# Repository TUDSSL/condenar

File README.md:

# TURNER Games Console

This is the official public repository for the TURNER battery-free gaming console.

<p align="center">
  <sub><strong>Figure 1.</strong> The battery-free TURNER console in action. Turning the crank enables weapon firing in DOOM while simultaneously generating energy to charge TURNER’s energy-storage capacitor. The capacitor’s charging state is shown by a small indicator at the top-right of the LCD panel. TURNER integrates solar energy harvesting, follows the form factor of a modern handheld game console, and features the standard “ABXY” button configuration. The current implementation weighs 509 g; the casing measures 24 cm × 14 cm × 3 cm, and the crank measures 2 cm × 6.5 cm × 2 cm.</sub>
</p>

## System Design Rationale

Battery-free computer gaming offers a vision of sustainable interaction in which games run on hardware that does not require a battery, yet this approach introduces uncertainty due to frequent power failures. Rather than viewing these failures as limitations, this work examines how integrating energy harvesting with application design can encourage users to reimagine and work with such failures, thus shaping behaviour and supporting device use. We present TURNER, a state-of-the-art modular battery-free games console powered by a hand crank and solar cells, created as a research probe to study how energy harvesting mediates the relationship between power and interaction. 

In a subsequent mixed-methods study (N = 60), we explored the influence of energy harvesting on gameplay. Findings show significant variations in harvesting strategies, with interviews surfacing strategies for creating applications that respond to and build on the patterns of system power failure, the ergonomics of energy harvesting, and the value of embedding energy generation into play. Our work offers insights for interactive, sustainable battery-free computers.

## Repository Structure

- [/Hardware](https://github.com/tudssl/condenar/tree/master/Hardware): This folder contains the source files for the hardware used in this project.
- [/Software](https://github.com/tudssl/condenar/tree/master/Software): The folder contains the software used in the TURNER console (including console firmware, apps, and logging software).
- [/Data](https://github.com/tudssl/condenar/tree/master/Data): This folder contains the data and data analysis scripts used in the TURNER user study.
- [/Doc-images](https://github.com/TUDSSL/condenar/tree/master/Doc-images): This folder contains images of the TURNER console. 

## TURNER System Description

<p align="center">
  <sub><strong>Figure 2.</strong> TURNER system implementation: (A) back of the COM50H5M81XLC transflective LCD screen; (B) logging module using an Espressif Systems ESP32 PICO Series microcontroller; (C) Central Processing Unit (CPU) module using an Ambiq Apollo4 MCU; (D) power management; (E) logging module battery; (F) solar module implemented around the Analog Devices LTC3129 Maximum Power Point Tracking (MPPT) buck-boost energy harvester; (G) crank module; (H) 6V 1.5F Kyocera AVX-SCM supercapacitor (SCMR22H155PSBB0); (I) ambient light sensor; (J) energy module connection points; (K) “ABXY” buttons; (L) solar panel connection on the front of the system casing. Eight ExCellLight EXL10-4V170 high-performance solar cells (50 mm × 20 mm each) are deployed; (M) joystick; (N) Universal Serial Bus (USB) port; (O) left trigger button; (P) right trigger button. The battery is used <em>only</em> to power the logging module and during the battery-powered console configuration experimental condition.</sub>
</p>

## TURNER User Study

The user study of TURNER employed a mixed-methods approach, combining console log data, questionnaire responses, and post-study interviews. The study was [pre-registed at Open Science Framework (OSF)](http://osf.io/7fp2w). 

### Quantitative Analysis

A range of statistical tests were used to assess the significance of effects in our log and questionnaire data. Parametric tests were applied when assumptions of normality, from Shapiro-Wilk, and homoscedasticity, from Levene's tests, were met. To analyse differences among more than two groups, we used Analysis of Variance (ANOVA) for between-subjects designs and repeated-measures ANOVA for within-subjects designs when parametric assumptions held, and Kruskal–Wallis or Friedman tests when non-parametric, respectively. Significant results were followed by post-hoc pairwise comparisons using Tukey’s HSD (parametric) or Dunn’s test with Bonferroni correction (non-parametric). For comparisons between two groups, we used independent samples t-tests or Mann-Whitney U tests, as appropriate. 

### Qualitative Analysis

We analysed post-study interviews using inductive thematic analysis, following the six-phase guidance proposed by [Braun and Clarke](https://www.tandfonline.com/doi/abs/10.1191/1478088706qp063oa). Coding was inductive, with initial descriptive and in vivo codes generated through repeated engagement with participants’ responses. Codes were iteratively refined and grouped into broader patterns through multiple rounds of analysis. 

## How to Cite This Work

The results of this project will be published in a peer-reviewed academic publication (from which all technical figures and most of the text in this file originate). Details of the publication are as follows.

* **Authors and the project team:** [James Scott Broadhead](https://scholar.google.com/citations?user=sMDFHlMAAAAJ), [Jasper de Winkel](https://jasperdewinkel.com), [Alejandro Cabrerizo Martinez de La Puente](https://www.linkedin.com/in/alejandro-cabrerizo-03780b136), [Himanshu Verma](https://vermahimanshu.com), [Przemysław Pawełczak](http://www.pawelczak.net)
* **Publication title:** _Connecting Power and Play: Investigating Interactive Energy Harvesting in Battery-Free Gaming_

<!--
* **Pulication venue:** [Proceedings of the 2026 CHI Conference on Human Factors in Computing Systems (CHI '26), April 13-17, 2026, Barcelona, Spain](https://dl.acm.org/)
* **Link to publication:** https://doi.org/10.1145/3772318.3790831 (Open Access)
* **Link to ACM CHI 2026 conference presentation video:** https://www.youtube.com/watch?
-->

<!--
To cite this publication please use the following BiBTeX entry.

```
@article{broadhead:chi:2026:turner,
  title = {Connecting Power and Play: Investigating Interactive Energy Harvesting in Battery-Free Gaming},
  author = {James Scott {Broadhead} and Jasper {de Winkel} and Alejandro Cabrerizo Martinez {de La Puente} and Himanshu {Verma} and Przemys{\l}aw {Pawe{\l}czak}},
  journal = {Proc. ACM Conference on Human Factors in Computing Systems (ACM CHI)},
  month =  apr # " 13--17",
  year = {2026},
  pages = {--},
  address = {Barcelona, Spain},
  publisher = {ACM}
}
```
-->

## Copyright

Copyright (C) 2026 TU Delft Embedded Systems Group/Sustainable Systems Laboratory.

MIT License or otherwise specified. See [license](https://github.com/TUDSSL/CONDENAR/blob/master/LICENSE) file for details.

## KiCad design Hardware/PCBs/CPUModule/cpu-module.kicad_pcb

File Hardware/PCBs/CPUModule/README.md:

# CPU-Module

KiCad project of the CPU module, including the schematic, PCB layout and BOM.

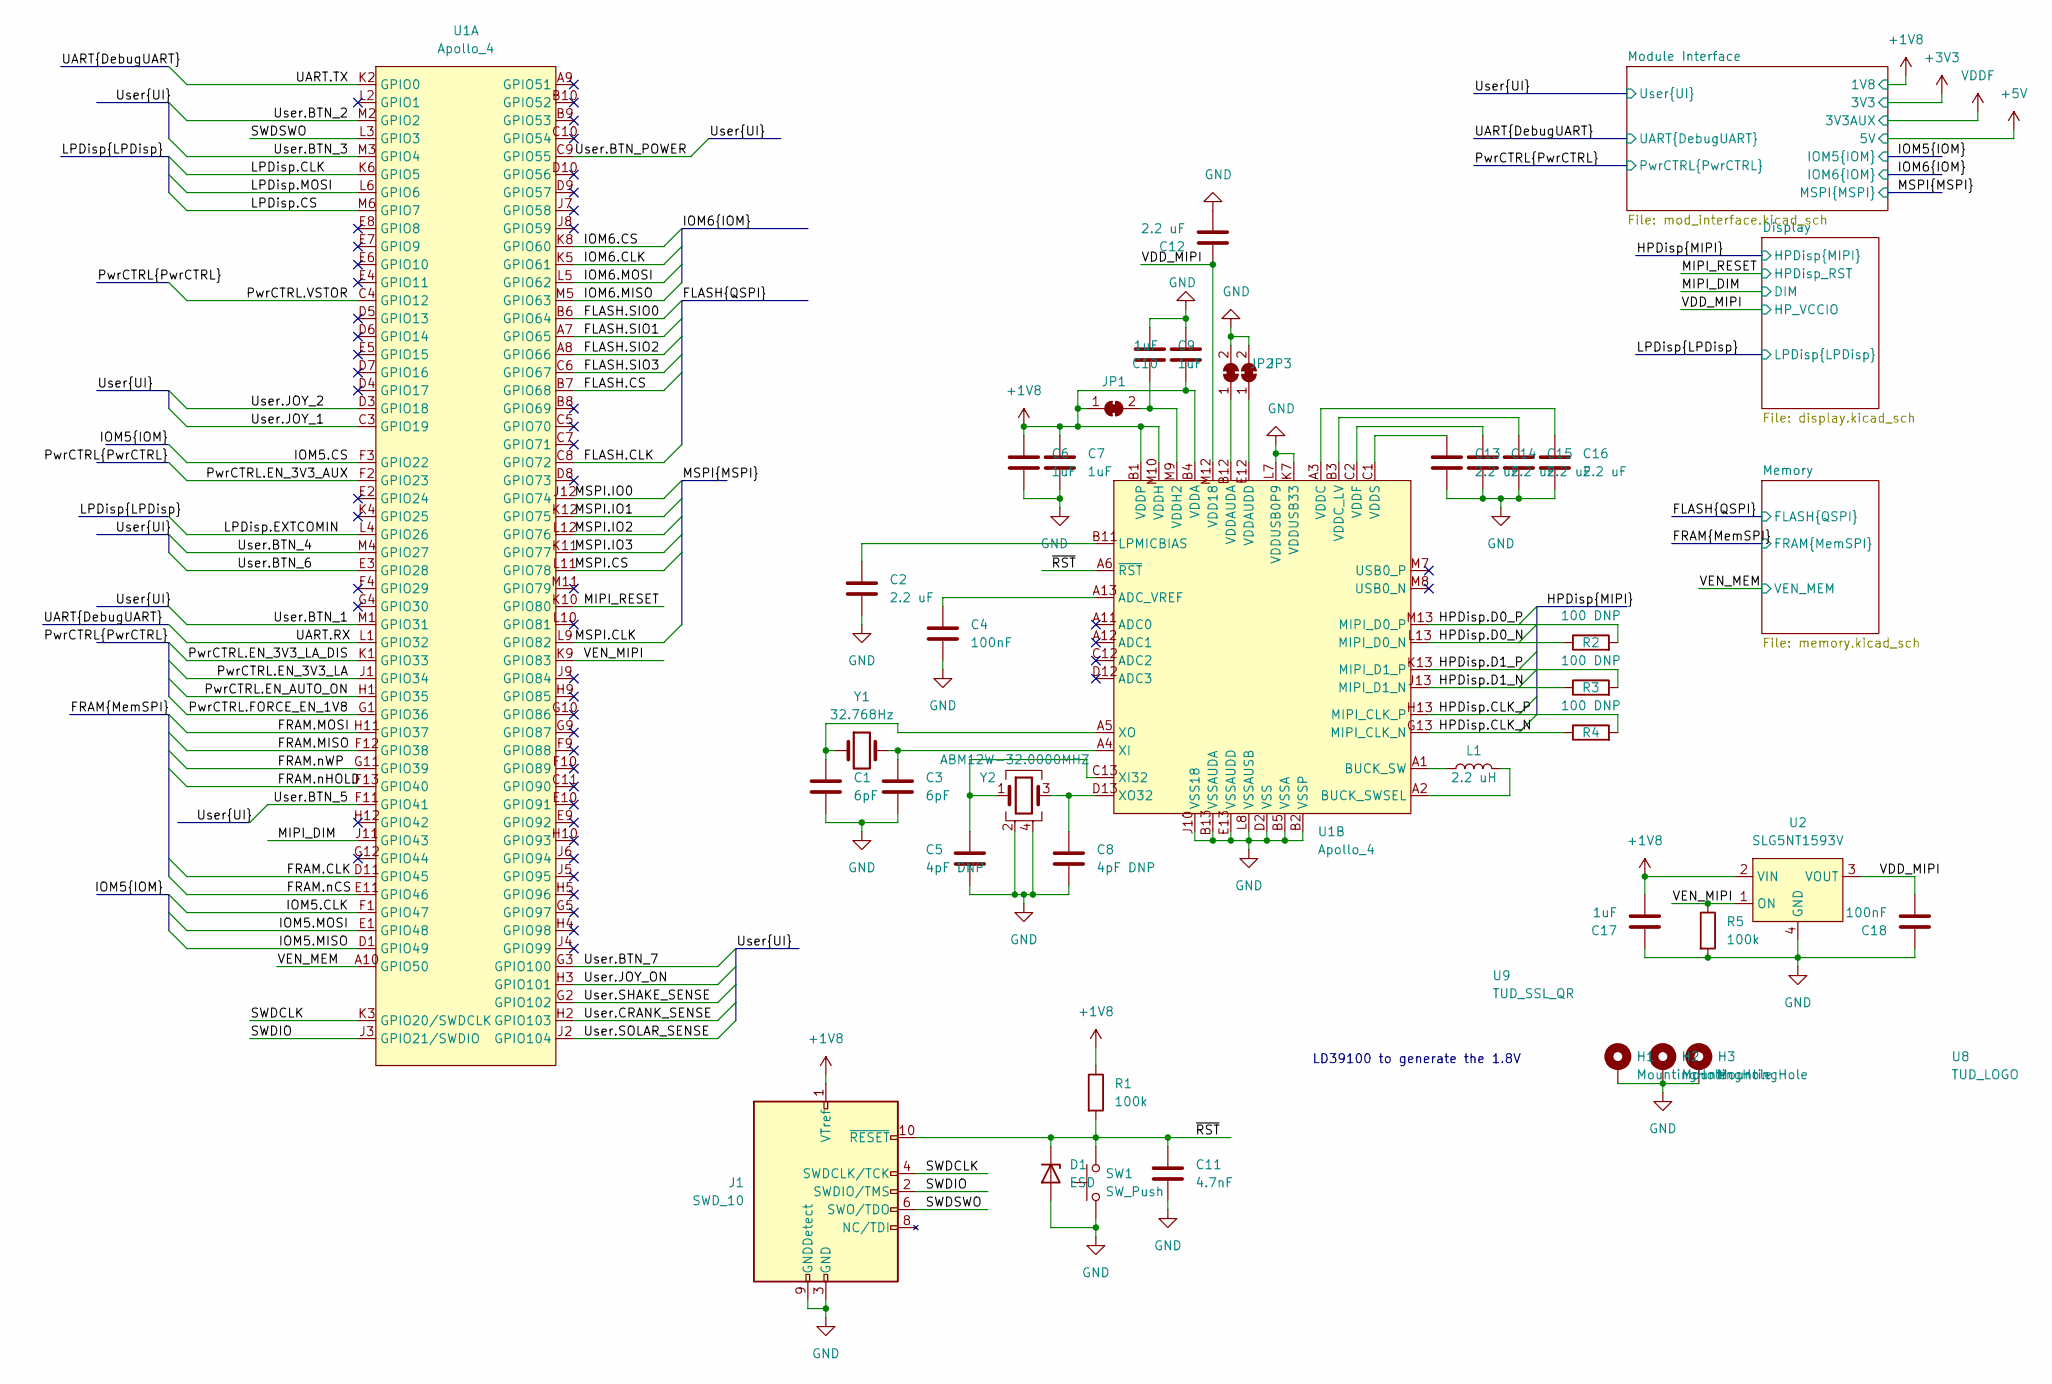
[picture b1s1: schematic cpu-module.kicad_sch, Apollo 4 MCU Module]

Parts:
C1, C3: 6pF; C_0402_1005Metric; MPN CC0402BRNPO9BN6R0
C2, C12, C13, C14, C15, C16: 2.2 uF; C_0201_0603Metric; MPN GRM033R61A225KE47D
C4, C18: 100nF; C_0402_1005Metric; MPN GRM155R71C104KA88J
C5, C8: 4pF DNP; C_0402_1005Metric; MPN CQ0402ARNPO9BN4R0
C6, C7, C9, C10: 1uF; C_0201_0603Metric; MPN GRM033C81A105ME05D
C11: 4.7nF; C_0201_0603Metric; MPN GRM033R61E472KA12D
C17: 1uF; C_0402_1005Metric; MPN CL05A105KP5NNNC
D1: ESD; D_SOD-523; MPN PESD5V0X1UB
H1, H2, H3: MountingHole; MountingHole_2.2mm_M2_Pad_Via
J1: SWD_10; ftsh-105-01-f-dv-k; MPN ftsh-105-01-f-dv-k
JP1, JP2, JP3: SolderJumper_2_Bridged; SolderJumper-small-nc
L1: 2.2 uH; L_0805_2012Metric; MPN DFE201210U-2R2M=P2
R1, R5: 100k; R_0402_1005Metric; MPN ERJ-2RKF1003X
R2, R3, R4: 100 DNP; R_0201_0603Metric; MPN CRCW0201100RFNED
SW1: SW_Push; SW_SPST_B3U-1000P; MPN B3U-1000P
U1: Apollo_4; Apollo4-BGA-156_13x12_5.0x5.0mm; MPN Apollo 4
U2: SLG5NT1593V; MPN SLG5NT1593V
U8: TUD_LOGO; DELFT_LOGO2
U9: TUD_SSL_QR; TUDSSL
Y1: 32.768Hz; Crystal_SMD_MicroCrystal_CM9V-T1A-2Pin_1.6x1.0mm; MPN 9HT12-32.768KDZY
Y2: ABM12W-32.0000MHZ; Crystal_SMD_Abracon_ABM12B-4Pin_1.6x1.2mm; MPN ABM12W-32.0000MHZ-6-D1X-T3

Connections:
+1V8: C6.1, C7.1, C10.1, C17.2, J1.1 (VTref), JP1.1 (A), R1.1, U1.B1 (VDDP), U1.B4 (VDDA), U1.M10 (VDDH), U2.2 (VIN); also elsewhere on the board
/FLASH.CLK: U1.C8 (GPIO72); also elsewhere on the board
/FLASH.CS: U1.B7 (GPIO68); also elsewhere on the board
/FLASH.SIO0: U1.B6 (GPIO64); also elsewhere on the board
/FLASH.SIO1: U1.A7 (GPIO65); also elsewhere on the board
/FLASH.SIO2: U1.A8 (GPIO66); also elsewhere on the board
/FLASH.SIO3: U1.C6 (GPIO67); also elsewhere on the board
/FRAM.CLK: U1.D11 (GPIO45); also elsewhere on the board
/FRAM.MISO: U1.F12 (GPIO38); also elsewhere on the board
/FRAM.MOSI: U1.H11 (GPIO37); also elsewhere on the board
/FRAM.nCS: U1.E11 (GPIO46); also elsewhere on the board
/FRAM.nHOLD: U1.F13 (GPIO40); also elsewhere on the board
/FRAM.nWP: U1.G11 (GPIO39); also elsewhere on the board
/HPDisp.CLK_N: R4.1, U1.G13 (MIPI_CLK_N); also elsewhere on the board
/HPDisp.CLK_P: R4.2, U1.H13 (MIPI_CLK_P); also elsewhere on the board
/HPDisp.D0_N: R2.1, U1.L13 (MIPI_D0_N); also elsewhere on the board
/HPDisp.D0_P: R2.2, U1.M13 (MIPI_D0_P); also elsewhere on the board
/HPDisp.D1_N: R3.1, U1.J13 (MIPI_D1_N); also elsewhere on the board
/HPDisp.D1_P: R3.2, U1.K13 (MIPI_D1_P); also elsewhere on the board
/IOM5.CLK: U1.F1 (GPIO47); also elsewhere on the board
/IOM5.CS: U1.F3 (GPIO22); also elsewhere on the board
/IOM5.MISO: U1.D1 (GPIO49); also elsewhere on the board
/IOM5.MOSI: U1.E1 (GPIO48); also elsewhere on the board
/IOM6.CLK: U1.K5 (GPIO61); also elsewhere on the board
/IOM6.CS: U1.K8 (GPIO60); also elsewhere on the board
/IOM6.MISO: U1.M5 (GPIO63); also elsewhere on the board
/IOM6.MOSI: U1.L5 (GPIO62); also elsewhere on the board
/LPDisp.CLK: U1.K6 (GPIO5); also elsewhere on the board
/LPDisp.CS: U1.M6 (GPIO7); also elsewhere on the board
/LPDisp.EXTCOMIN: U1.L4 (GPIO26); also elsewhere on the board
/LPDisp.MOSI: U1.L6 (GPIO6); also elsewhere on the board
/MIPI_DIM: U1.J11 (GPIO43); also elsewhere on the board
/MIPI_RESET: U1.K10 (GPIO80); also elsewhere on the board
/MSPI.CLK: U1.L9 (GPIO82); also elsewhere on the board
/MSPI.CS: U1.L11 (GPIO78); also elsewhere on the board
/MSPI.IO0: U1.J12 (GPIO74); also elsewhere on the board
/MSPI.IO1: U1.K12 (GPIO75); also elsewhere on the board
/MSPI.IO2: U1.L12 (GPIO76); also elsewhere on the board
/MSPI.IO3: U1.K11 (GPIO77); also elsewhere on the board
/PwrCTRL.EN_3V3_AUX: U1.F2 (GPIO23); also elsewhere on the board
/PwrCTRL.EN_3V3_LA: U1.J1 (GPIO34); also elsewhere on the board
/PwrCTRL.EN_3V3_LA_DIS: U1.K1 (GPIO33); also elsewhere on the board
/PwrCTRL.EN_AUTO_ON: U1.H1 (GPIO35); also elsewhere on the board
/PwrCTRL.FORCE_EN_1V8: U1.G1 (GPIO36); also elsewhere on the board
/PwrCTRL.VSTOR: U1.C4 (GPIO12); also elsewhere on the board
/SWDCLK: J1.4 (SWDCLK/TCK), U1.K3 (GPIO20/SWDCLK)
/SWDIO: J1.2 (SWDIO/TMS), U1.J3 (GPIO21/SWDIO)
/SWDSWO: J1.6 (SWO/TDO), U1.L3 (GPIO3)
/UART.RX: U1.L1 (GPIO32); also elsewhere on the board
/UART.TX: U1.K2 (GPIO0); also elsewhere on the board
/User.BTN_1: U1.M1 (GPIO31); also elsewhere on the board
/User.BTN_2: U1.M2 (GPIO2); also elsewhere on the board
/User.BTN_3: U1.M3 (GPIO4); also elsewhere on the board
/User.BTN_4: U1.M4 (GPIO27); also elsewhere on the board
/User.BTN_5: U1.F11 (GPIO41); also elsewhere on the board
/User.BTN_6: U1.E3 (GPIO28); also elsewhere on the board
/User.BTN_7: U1.G3 (GPIO100); also elsewhere on the board
/User.BTN_POWER: U1.C9 (GPIO55); also elsewhere on the board
/User.CRANK_SENSE: U1.H2 (GPIO103); also elsewhere on the board
/User.JOY_1: U1.C3 (GPIO19); also elsewhere on the board
/User.JOY_2: U1.D3 (GPIO18); also elsewhere on the board
/User.JOY_ON: U1.H3 (GPIO101); also elsewhere on the board
/User.SHAKE_SENSE: U1.G2 (GPIO102); also elsewhere on the board
/User.SOLAR_SENSE: U1.J2 (GPIO104); also elsewhere on the board
/VDD_MIPI: C12.1, C18.2, U1.M12 (VDD18), U2.3 (VOUT); also elsewhere on the board
/VEN_MEM: U1.A10 (GPIO50); also elsewhere on the board
/VEN_MIPI: R5.1, U1.K9 (GPIO83), U2.1 (ON)
/~RST: C11.1, D1.1 (K), J1.10 (~RESET), R1.2, SW1.2, U1.A6 (~RST)
GND: C1.2, C2.2, C3.2, C4.2, C5.2, C6.2, C7.2, C8.2, C9.2, C10.2, C11.2, C12.2, C13.2, C14.2, C15.2, C16.2, C17.1, C18.1, D1.2 (A), H1.1, H2.1, H3.1, J1.3 (GND), J1.5 (GND), J1.9 (GNDDetect), JP2.2 (B), JP3.2 (B), R5.2, SW1.1, U1.B2 (VSSP), U1.B5 (VSSA), U1.B13 (VSSAUDA), U1.D2 (VSS), U1.E13 (VSSAUDD), U1.J10 (VSS18), U1.K7 (VDDUSB33), U1.L7 (VDDUSB0P9), U1.L8 (VSSAUSB), U2.4 (GND), Y2.2, Y2.4; also elsewhere on the board
unnamed: C1.1, U1.A5 (XO), Y1.1
unnamed: C2.1, U1.B11 (LPMICBIAS)
unnamed: C3.1, U1.A4 (XI), Y1.2
unnamed: C4.1, U1.A13 (ADC_VREF)
unnamed: C5.1, U1.C13 (XI32), Y2.1
unnamed: C8.1, U1.D13 (XO32), Y2.3
unnamed: C9.1, JP1.2 (B), U1.M9 (VDDH2)
unnamed: C13.1, U1.C1 (VDDS)
unnamed: C14.1, U1.C2 (VDDF)
unnamed: C15.1, U1.B3 (VDDC_LV)
unnamed: C16.1, U1.A3 (VDDC)
unnamed: JP2.1 (A), U1.B12 (VDDAUDA)
unnamed: JP3.1 (A), U1.E12 (VDDAUDD)
unnamed: L1.1, U1.A1 (BUCK_SW)
unnamed: L1.2, U1.A2 (BUCK_SWSEL)

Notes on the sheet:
LD39100 to generate the 1.8V

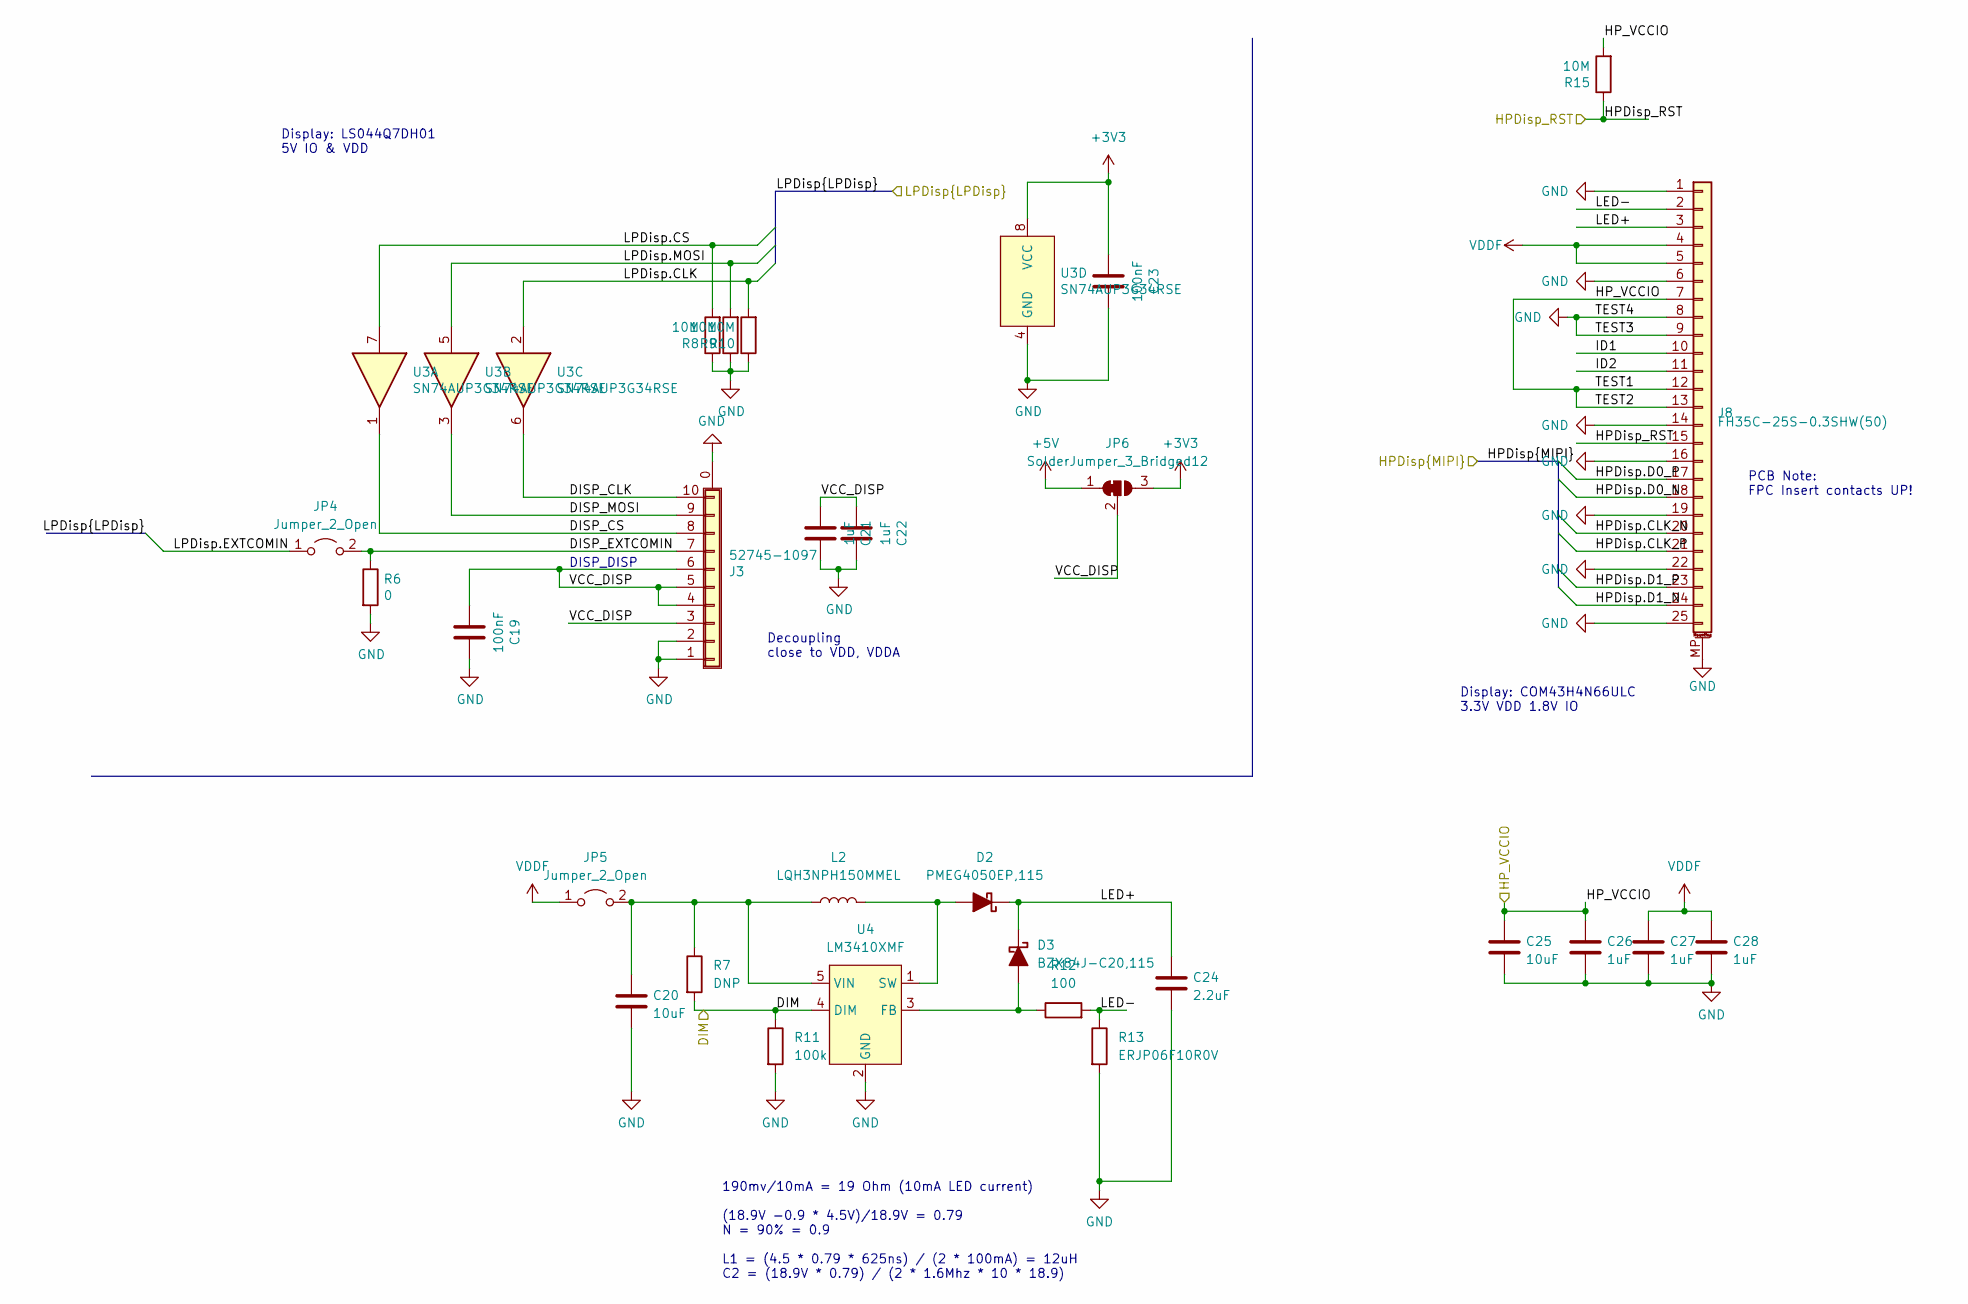
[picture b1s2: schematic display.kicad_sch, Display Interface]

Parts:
C19, C23: 100nF; C_0402_1005Metric; MPN GRM155R71C104KA88J
C20: 10uF; C_0603_1608Metric; MPN GRT188R61C106KE13D
C21, C22, C26, C27, C28: 1uF; C_0402_1005Metric; MPN CL05A105KP5NNNC
C24: 2.2uF; C_0603_1608Metric; MPN GRM188R61H225KE11D
C25: 10uF; C_0402_1005Metric; MPN CL05A106MP8NUB8
D2: PMEG4050EP,115; D_SOD-128; MPN PMEG4050EP,115
D3: BZX84J-C20,115; D_SOD-323F; MPN BZX84J-C20,115
J3: 52745-1097; FPC_10_TOP; MPN 52745-1097
J8: FH35C-25S-0.3SHW(50); FH35C-25S-0.3SHW_2Rows-27Pins-1MP_P0.60mm_Horizontal; MPN FH35C-25S-0.3SHW(50)
JP4, JP5: Jumper_2_Open; SolderJumper-small-no-150um
JP6: SolderJumper_3_Bridged12; SolderJumper-3_P1.3mm_Bridged12_RoundedPad1.0x1.5mm
L2: LQH3NPH150MMEL; VLS6045EX; MPN LQH3NPH150MMEL
R6: 0; R_0402_1005Metric; MPN ERJ-2GE0R00X
R7: DNP; R_0603_1608Metric
R8, R9, R10, R15: 10M; R_0402_1005Metric; MPN RC0402FR-0710ML
R11: 100k; R_0603_1608Metric; MPN ERJ-3EKF1003V
R12: 100; R_0603_1608Metric; MPN CRCW0603100RFKEAHP
R13: ERJP06F10R0V; R_0805_2012Metric; MPN ERJP06F10R0V
U3: SN74AUP3G34RSE; Texas_RSE_8_UQFN; MPN SN74AUP3G34RSE
U4: LM3410XMF; SOT-23-5; MPN LM3410XMF

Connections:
+3V3: C23.1, JP6.3 (B), U3.8 (VCC); also elsewhere on the board
+5V: JP6.1 (A); also elsewhere on the board
/Display/DISP_CLK: J3.10, U3.6
/Display/DISP_CS: J3.8, U3.1
/Display/DISP_EXTCOMIN: J3.7, JP4.2 (B), R6.1
/Display/DISP_MOSI: J3.9, U3.3
/Display/ID1: J8.10
/Display/ID2: J8.11
/Display/LED+: C24.1, D2.1 (K), D3.1 (K), J8.3
/Display/LED-: J8.2, R12.2, R13.1
/Display/VCC_DISP: C19.1, C21.1, C22.1, J3.3, J3.4, J3.5, J3.6, JP6.2 (C)
/HPDisp.CLK_N: J8.20; also elsewhere on the board
/HPDisp.CLK_P: J8.21; also elsewhere on the board
/HPDisp.D0_N: J8.18; also elsewhere on the board
/HPDisp.D0_P: J8.17; also elsewhere on the board
/HPDisp.D1_N: J8.24; also elsewhere on the board
/HPDisp.D1_P: J8.23; also elsewhere on the board
/LPDisp.CLK: R10.2, U3.2; also elsewhere on the board
/LPDisp.CS: R8.2, U3.7; also elsewhere on the board
/LPDisp.EXTCOMIN: JP4.1 (A); also elsewhere on the board
/LPDisp.MOSI: R9.2, U3.5; also elsewhere on the board
/MIPI_DIM: R7.2, R11.1, U4.4 (DIM); also elsewhere on the board
/MIPI_RESET: J8.15, R15.1; also elsewhere on the board
/VDD_MIPI: C25.1, C26.1, J8.7, J8.12, J8.13, R15.2; also elsewhere on the board
GND: C19.2, C20.2, C21.2, C22.2, C23.2, C24.2, C25.2, C26.2, C27.2, C28.2, J3.0 (Shield), J3.1, J3.2, J8.1, J8.6, J8.8, J8.9, J8.14, J8.16, J8.19, J8.22, J8.25, J8.MP (MountPin), R6.2, R8.1, R9.1, R10.1, R11.2, R13.2, U3.4 (GND), U4.2 (GND); also elsewhere on the board
unnamed: C20.1, JP5.2 (B), L2.1, R7.1, U4.5 (VIN)
unnamed: D2.2 (A), L2.2, U4.1 (SW)
unnamed: D3.2 (A), R12.1, U4.3 (FB)
VDDF: C27.1, C28.1, J8.4, J8.5, JP5.1 (A); also elsewhere on the board

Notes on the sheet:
190mv/10mA = 19 Ohm (10mA LED current) (18.9V -0.9 * 4.5V)/18.9V = 0.79 N = 90% = 0.9 L1 = (4.5 * 0.79 * 625ns) / (2 * 100mA) = 12uH C2 = (18.9V * 0.79) / (2 * 1.6Mhz * 10 * 18.9)
Display: COM43H4N66ULC 3.3V VDD 1.8V IO
Decoupling close to VDD, VDDA
DISP_DISP
PCB Note: FPC Insert contacts UP!
Display: LS044Q7DH01 5V IO & VDD

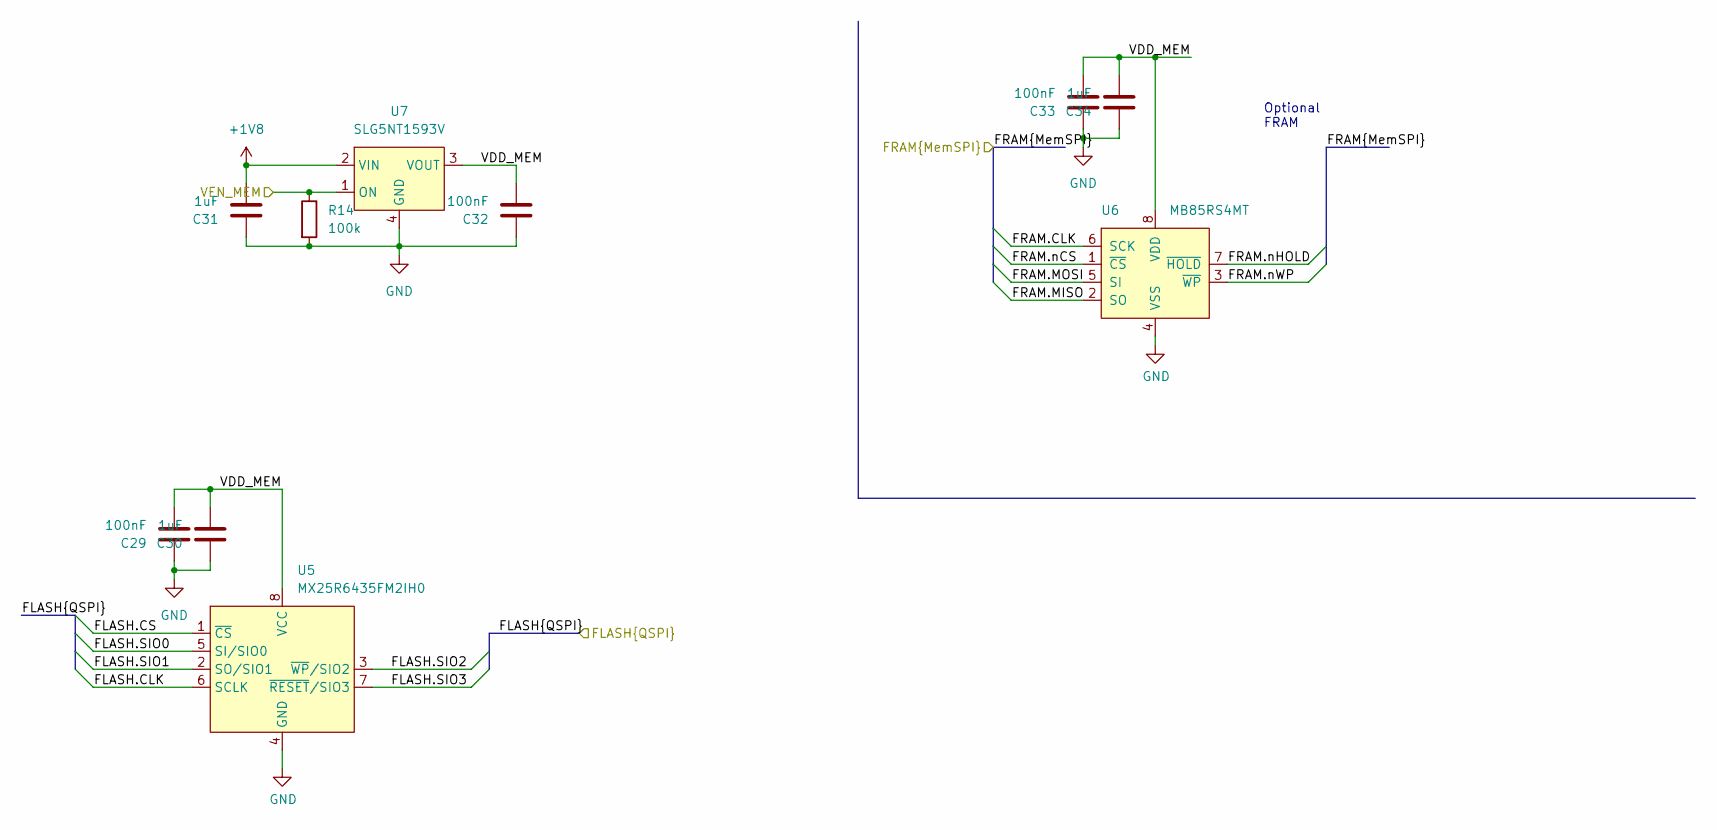
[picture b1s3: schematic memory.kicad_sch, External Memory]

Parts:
C29, C32, C33: 100nF; C_0402_1005Metric; MPN GRM155R71C104KA88J
C30, C31, C34: 1uF; C_0402_1005Metric; MPN CL05A105KP5NNNC
R14: 100k; R_0402_1005Metric; MPN ERJ-2RKF1003X
U5: MX25R6435FM2IH0; SOP-8_5.28x5.23mm_P1.27mm; MPN MX25R6435FM2IH0
U6: MB85RS4MT; SO-8_5.3x6.2mm_P1.27mm; MPN MB85RS4MT
U7: SLG5NT1593V; MPN SLG5NT1593V

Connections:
+1V8: C31.2, U7.2 (VIN); also elsewhere on the board
/FLASH.CLK: U5.6 (SCLK); also elsewhere on the board
/FLASH.CS: U5.1 (~CS); also elsewhere on the board
/FLASH.SIO0: U5.5 (SI/SIO0); also elsewhere on the board
/FLASH.SIO1: U5.2 (SO/SIO1); also elsewhere on the board
/FLASH.SIO2: U5.3 (~WP/SIO2); also elsewhere on the board
/FLASH.SIO3: U5.7 (~RESET/SIO3); also elsewhere on the board
/FRAM.CLK: U6.6 (SCK); also elsewhere on the board
/FRAM.MISO: U6.2 (SO); also elsewhere on the board
/FRAM.MOSI: U6.5 (SI); also elsewhere on the board
/FRAM.nCS: U6.1 (~CS); also elsewhere on the board
/FRAM.nHOLD: U6.7 (~HOLD); also elsewhere on the board
/FRAM.nWP: U6.3 (~WP); also elsewhere on the board
/Memory/VDD_MEM: C29.2, C30.2, C32.2, C33.2, C34.2, U5.8 (VCC), U6.8 (VDD), U7.3 (VOUT)
/VEN_MEM: R14.1, U7.1 (ON); also elsewhere on the board
GND: C29.1, C30.1, C31.1, C32.1, C33.1, C34.1, R14.2, U5.4 (GND), U6.4 (VSS), U7.4 (GND); also elsewhere on the board

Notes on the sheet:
Optional FRAM

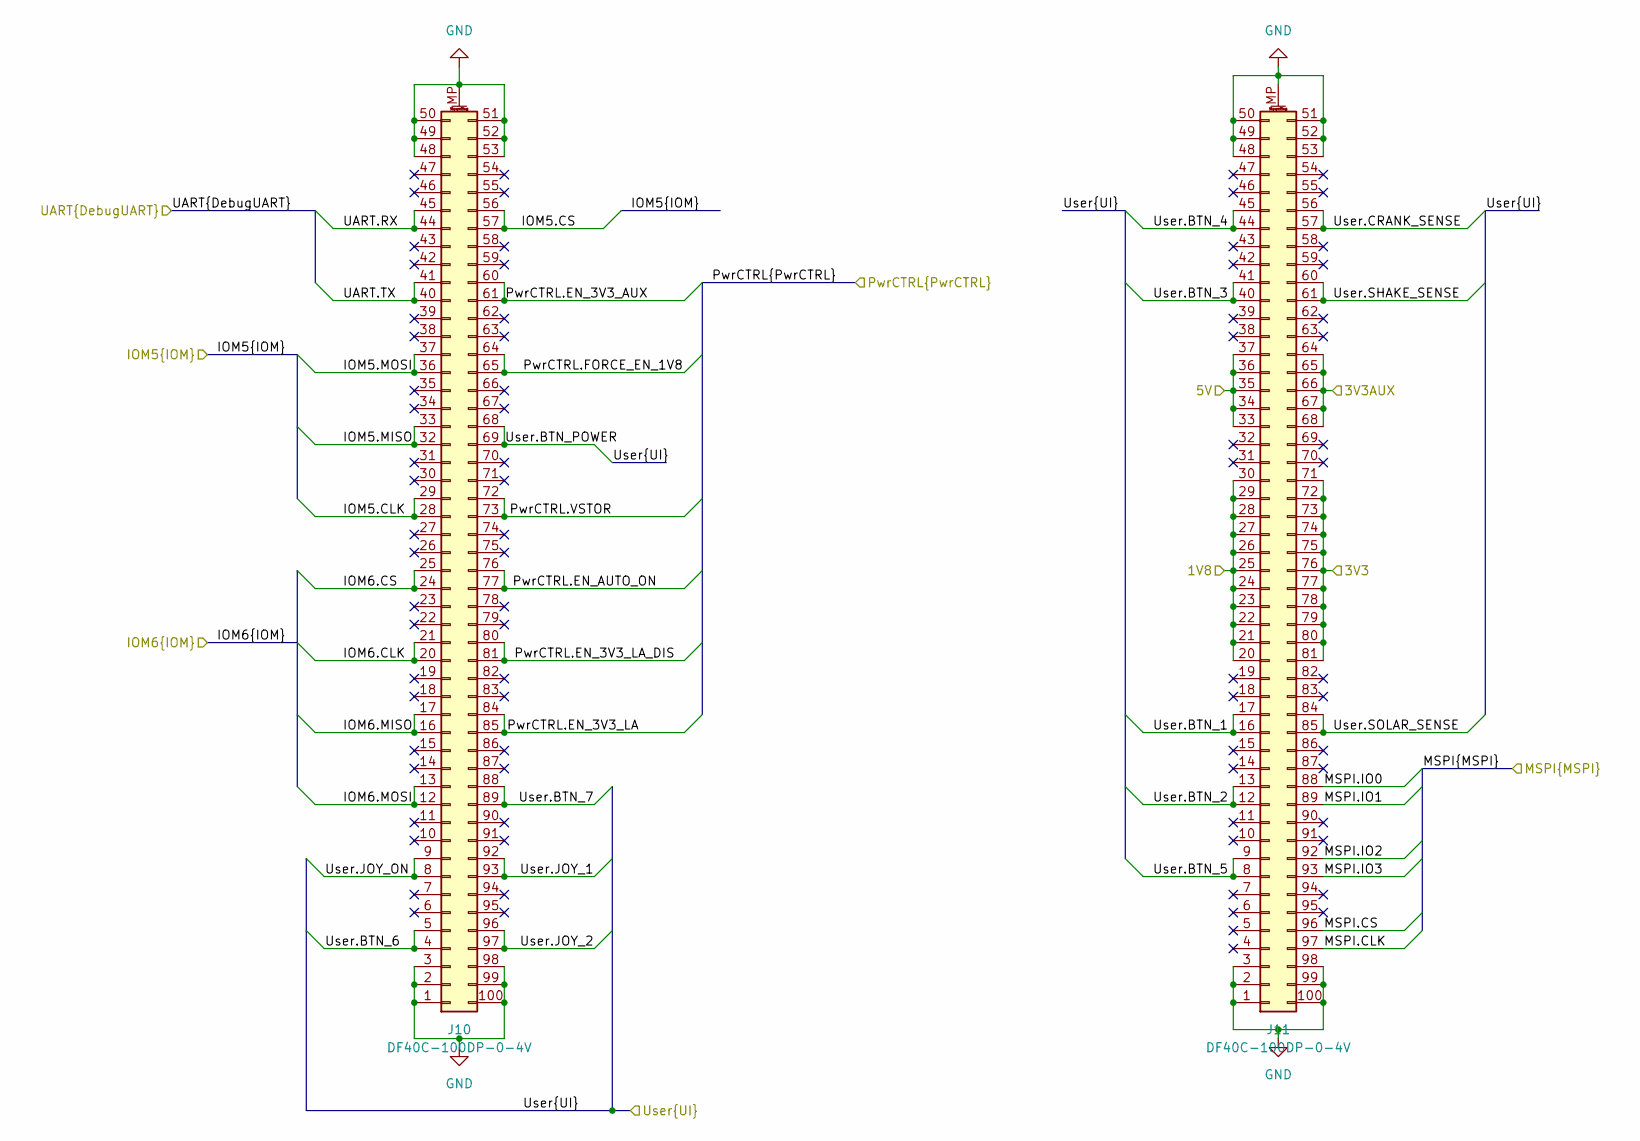
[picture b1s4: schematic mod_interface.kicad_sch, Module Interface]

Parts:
J10, J11: DF40C-100DP-0-4V; DF40C-100DP; MPN DF40C-100DP-0-4V

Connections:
+1V8: J11.20, J11.21, J11.22, J11.23, J11.24, J11.25, J11.26, J11.27, J11.28, J11.29, J11.30; also elsewhere on the board
+3V3: J11.71, J11.72, J11.73, J11.74, J11.75, J11.76, J11.77, J11.78, J11.79, J11.80, J11.81; also elsewhere on the board
+5V: J11.33, J11.34, J11.35, J11.36, J11.37; also elsewhere on the board
/IOM5.CLK: J10.28, J10.29; also elsewhere on the board
/IOM5.CS: J10.56, J10.57; also elsewhere on the board
/IOM5.MISO: J10.32, J10.33; also elsewhere on the board
/IOM5.MOSI: J10.36, J10.37; also elsewhere on the board
/IOM6.CLK: J10.20, J10.21; also elsewhere on the board
/IOM6.CS: J10.24, J10.25; also elsewhere on the board
/IOM6.MISO: J10.16, J10.17; also elsewhere on the board
/IOM6.MOSI: J10.12, J10.13; also elsewhere on the board
/MSPI.CLK: J11.97; also elsewhere on the board
/MSPI.CS: J11.96; also elsewhere on the board
/MSPI.IO0: J11.88; also elsewhere on the board
/MSPI.IO1: J11.89; also elsewhere on the board
/MSPI.IO2: J11.92; also elsewhere on the board
/MSPI.IO3: J11.93; also elsewhere on the board
/PwrCTRL.EN_3V3_AUX: J10.60, J10.61; also elsewhere on the board
/PwrCTRL.EN_3V3_LA: J10.84, J10.85; also elsewhere on the board
/PwrCTRL.EN_3V3_LA_DIS: J10.80, J10.81; also elsewhere on the board
/PwrCTRL.EN_AUTO_ON: J10.76, J10.77; also elsewhere on the board
/PwrCTRL.FORCE_EN_1V8: J10.64, J10.65; also elsewhere on the board
/PwrCTRL.VSTOR: J10.72, J10.73; also elsewhere on the board
/UART.RX: J10.44, J10.45; also elsewhere on the board
/UART.TX: J10.40, J10.41; also elsewhere on the board
/User.BTN_1: J11.16, J11.17; also elsewhere on the board
/User.BTN_2: J11.12, J11.13; also elsewhere on the board
/User.BTN_3: J11.40, J11.41; also elsewhere on the board
/User.BTN_4: J11.44, J11.45; also elsewhere on the board
/User.BTN_5: J11.8, J11.9; also elsewhere on the board
/User.BTN_6: J10.4, J10.5; also elsewhere on the board
/User.BTN_7: J10.88, J10.89; also elsewhere on the board
/User.BTN_POWER: J10.68, J10.69; also elsewhere on the board
/User.CRANK_SENSE: J11.56, J11.57; also elsewhere on the board
/User.JOY_1: J10.92, J10.93; also elsewhere on the board
/User.JOY_2: J10.96, J10.97; also elsewhere on the board
/User.JOY_ON: J10.8, J10.9; also elsewhere on the board
/User.SHAKE_SENSE: J11.60, J11.61; also elsewhere on the board
/User.SOLAR_SENSE: J11.84, J11.85; also elsewhere on the board
GND: J10.1, J10.2, J10.3, J10.48, J10.49, J10.50, J10.51, J10.52, J10.53, J10.98, J10.99, J10.100, J10.MP (MountPin), J11.1, J11.2, J11.3, J11.48, J11.49, J11.50, J11.51, J11.52, J11.53, J11.98, J11.99, J11.100, J11.MP (MountPin); also elsewhere on the board
VDDF: J11.64, J11.65, J11.66, J11.67, J11.68; also elsewhere on the board
